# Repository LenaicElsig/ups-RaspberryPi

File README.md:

# ups-RaspberryPi
Uninterrupted power supply for Raspberry Pi
This project has been developped during a 3-months traineeship in the Hes-so Valais.
The goal was to design a open-source uninterrupted power supply for the Raspberry-Pi, in case of a power failure such
as someone unplugging it. It is made with components easily available online, and can be mounted on a pcb board.
It features : a single cel li-po, a step up 3.7v -> 5v, a battery charger, power indication and reset-shutdown buttons for the Raspberry Pi. It can be directly plugged on the Pi, and only a single power supply is needed.

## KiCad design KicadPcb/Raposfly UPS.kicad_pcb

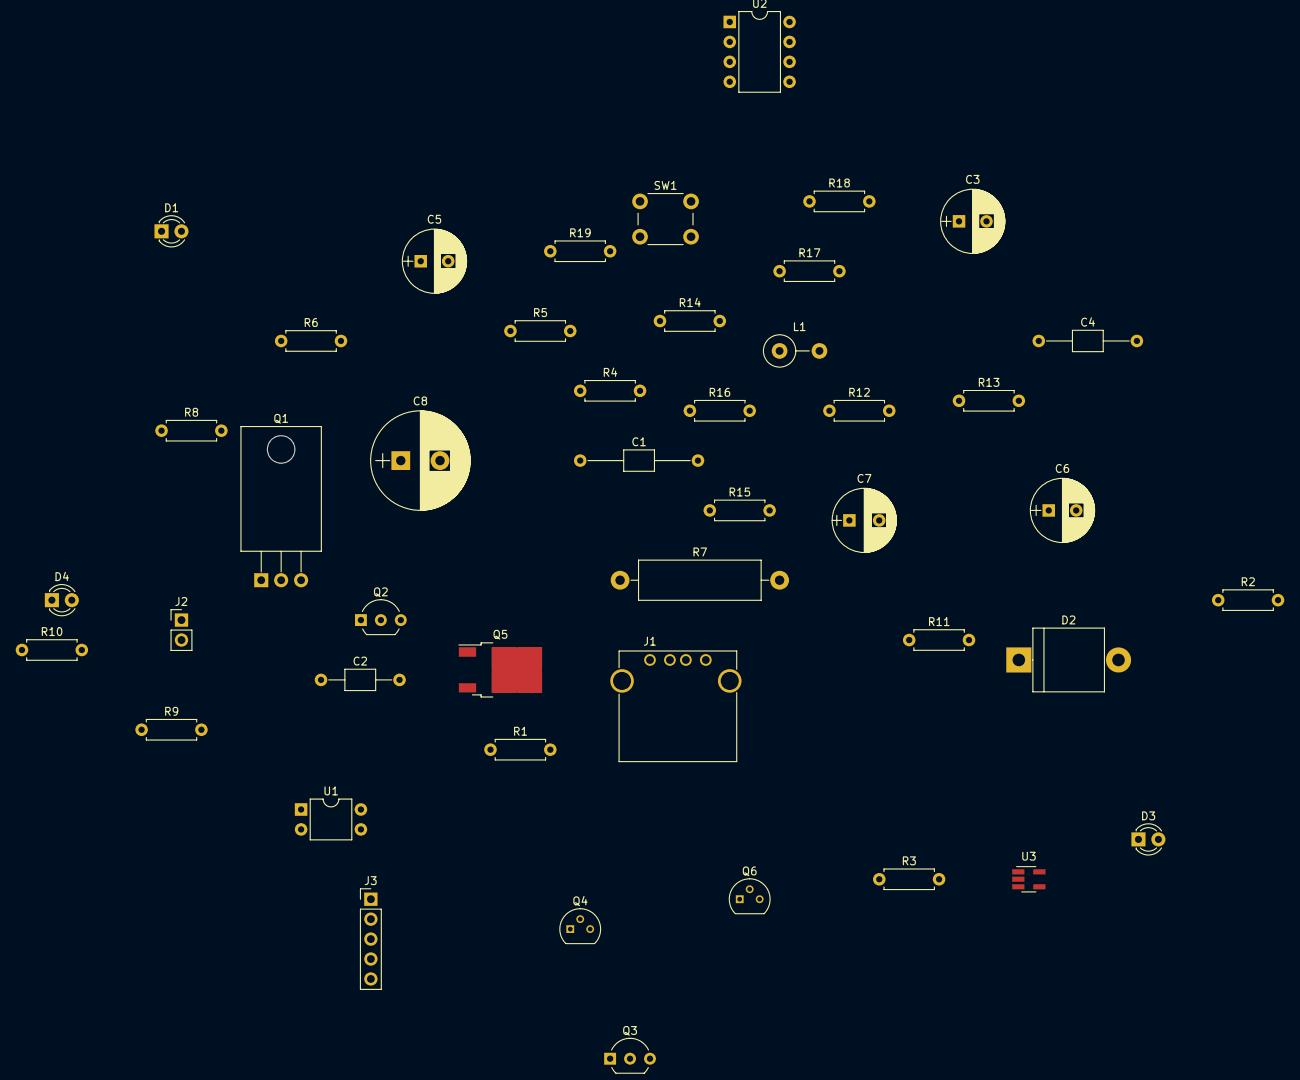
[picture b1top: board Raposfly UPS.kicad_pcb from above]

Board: 2 copper layers, 45 parts (0 on the bottom side), 25 nets, no tracks yet.

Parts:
C1: 100nF; C_Axial_L3.8mm_D2.6mm_P15.00mm_Horizontal
C2: 100pF; C_Axial_L3.8mm_D2.6mm_P10.00mm_Horizontal
C3, C5: 330uF; CP_Radial_D8.0mm_P3.50mm
C4: 100nF; C_Axial_L3.8mm_D2.6mm_P12.50mm_Horizontal
C6: 4.7uF; CP_Radial_D8.0mm_P3.50mm
C7: 4.7uF; CP_Radial_D8.0mm_P3.80mm
C8: 2300uF; CP_Radial_D12.5mm_P5.00mm
D1, D3, D4: LED; LED_D3.0mm
D2: 1N5822; D_5KPW_P12.70mm_Horizontal
J1: USB_A
J2: Conn_01x02_Female; Socket_Strip_Straight_1x02_Pitch2.54mm
J3: Conn_01x05_Female; Socket_Strip_Straight_1x05_Pitch2.54mm
L1: 22uH; L_Axial_L9.5mm_D4.0mm_P5.08mm_Vertical_Fastron_SMCC
Q1: IRLIZ44N; TO-220_Horizontal
Q2: bs170; TO-92_Inline_Wide
Q3: bs250; TO-92_Inline_Wide
Q4, Q6: BC327; TO-92_Molded_Narrow
Q5: sud50p04; TO-252-2
R1, R16: 3.3k; R_Axial_DIN0207_L6.3mm_D2.5mm_P7.62mm_Horizontal
R2: 5.6k; R_Axial_DIN0207_L6.3mm_D2.5mm_P7.62mm_Horizontal
R3: 82k; R_Axial_DIN0207_L6.3mm_D2.5mm_P7.62mm_Horizontal
R4, R8, R12: 100k; R_Axial_DIN0207_L6.3mm_D2.5mm_P7.62mm_Horizontal
R5: 33k; R_Axial_DIN0207_L6.3mm_D2.5mm_P7.62mm_Horizontal
R6, R13, R14: 470; R_Axial_DIN0207_L6.3mm_D2.5mm_P7.62mm_Horizontal
R7: 25mili; R_Axial_DIN0516_L15.5mm_D5.0mm_P20.32mm_Horizontal
R9, R10, R18: 1k; R_Axial_DIN0207_L6.3mm_D2.5mm_P7.62mm_Horizontal
R11: 2k; R_Axial_DIN0207_L6.3mm_D2.5mm_P7.62mm_Horizontal
R15, R19: 100; R_Axial_DIN0207_L6.3mm_D2.5mm_P7.62mm_Horizontal
R17: 6.8k; R_Axial_DIN0207_L6.3mm_D2.5mm_P7.62mm_Horizontal
SW1: SW_DPST_x2; SW_PUSH_6mm
U1: LF355; DIP-4_W7.62mm
U2: max1771; DIP-8_W7.62mm
U3: MCP7383; SOT-23-5_HandSoldering

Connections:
/5v_stepUp: C1.1, C2.2, C5.1, C8.1, D2.1, J3.1, Q3.1, Q5.3, Q6.3, R1.1, R3.2, SW1.1, U2.2
/5v_usb: C6.1, D3.2, J1.1, Q3.2, Q4.3, Q5.1, R4.1, R6.1, R12.1, R16.1, U2.4, U3.4
/batterie_+: C3.1, C7.1, J2.2, L1.2, U1.2, U3.3
/gpio14/8: J3.3, R9.2
/gpio15/10: J3.4, R10.2
/gpio18/12: J3.5, R16.2, R17.1
/shutdown: Q2.2, R8.1, SW1.2
GND: C1.2, C3.2, C4.2, C5.2, C6.2, C7.2, C8.2, D1.1, D4.1, J1.4, J2.1, J3.2, Q2.3, R2.2, R4.2, R5.2, R7.2, R8.2, R12.2, R15.2, R17.2, R18.2, R19.2, U1.1, U1.4, U2.6, U2.7
unnamed: C2.1, R3.1, R5.1, U2.3
unnamed: C4.1, U2.5
unnamed: D1.2, R6.2
unnamed: D2.2, L1.1, Q1.1
unnamed: D3.1, R13.1
unnamed: D4.2, R14.2
unnamed: Q1.2, U2.1
unnamed: Q1.3, R7.1, U2.8
unnamed: Q2.1, R9.1
unnamed: Q3.3, R14.1
unnamed: Q4.1, R15.1
unnamed: Q4.2, Q6.2, R18.1
unnamed: Q5.2, Q6.1, R19.1
unnamed: R1.2, R2.1, U1.3
unnamed: R11.1, U3.5
unnamed: R11.2, U3.2
unnamed: R13.2, U3.1

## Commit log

2017-11-23 this is my first committhing !
2017-11-23 Added documentation about the project
2017-11-23 Add .odt doc
2017-11-23 Added pcb layout for Kicad
2017-11-23 Added list of parts
2017-11-23 new images yeah !
